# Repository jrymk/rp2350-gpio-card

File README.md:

# rp2350-gpio-card
Expansion Card circuit based on RP2350 for Framework mainboards providing GPIO to the computer. Circuit is based on [Expansion Card template](https://github.com/FrameworkComputer/ExpansionCards) and [RP2350A Minimal board](https://datasheets.raspberrypi.com/rp2350/hardware-design-with-rp2350.pdf). Designed in [KiCad](https://www.kicad.org/). It got produced and assembled. Its fully functional. A 3D case for the card is made by XenoCow and [its files are available on Printables.com](https://www.printables.com/model/1445941-framework-expansion-card-case-for-typec-950-arp24).

## Gallery
* Real photo of card with TYPEC-950-ARP24 produced by NextPCB

* Render of card with Molex 1054440011 (Framework template)

* Render of card with TYPEC-950-ARP24 (NextPCB template)

## GPIO
### Front
| Label | Name   | SPI       | UART       | I2C        | ADC |
| :---- | :----- | :-------- | :--------- | :--------- | :-- |
| 0     | GPIO0  | SPI0 RX   | UART0 TX   | I2C0 SDA   |     |
| 1     | GPIO1  | SPI0 CSn  | UART0 RX   | I2C0 SCL   |     |
| 2     | GPIO2  | SPI0 SCK  |            | I2C1 SDA   |     |
| 3     | GPIO3  | SPI0 TX   |            | I2C1 SCL   |     |
| 4     | GPIO4  | SPI0 RX   | UART1 TX   | I2C0 SDA   |     |
| 5     | GPIO5  | SPI0 CSn  | UART1 RX   | I2C0 SCL   |     |
| 6     | GPIO6  | SPI0 SCK  |            | I2C1 SDA   |     |
| 7     | GPIO7  | SPI0 TX   |            | I2C1 SCL   |     |
| VCC   | 3.3v   |           |            |            |     |
| R     | Reset  |           |            |            |     |

### Back
| Label | Name   | SPI       | UART       | I2C        | ADC   |
| :---- | :----- | :-------- | :--------- | :--------- | :---- |
| 29    | GPIO29 |           |            |            | ADC3  |
| 28    | GPIO28 |           |            |            | ADC2  |
| 27    | GPIO27 |           |            | I2C1 SDL   | ADC1  |
| G     | Ground |           |            |            |       |
| 13    | GPIO13 | SPI1 CSN  | UART0 RX   | I2C0 SCL   |       |
| 12    | GPIO12 | SPI1 RX   | UART0 TX   | I2C0 SDA   |       |
| 11    | GPIO11 | SPI1 TX   |            | I2C1 SCL   |       |
| 10    | GPIO10 | SPI1 SCK  |            | I2C1 SDA   |       |
| 9     | GPIO9  | SPI1 CSn  | UART1 RX   | I2C0 SCL   |       |
| B     | Boot   |           |            |            |       |

## License
Designed by: [Tan Siret Akıncı](https://github.com/tansiret).
Schematics and footprint are licensed with [CC BY 4.0](LICENSE).
Politecnico di Torino name used in this project is © 2025 Politecnico di Torino. The project is sponsored by © 2025 [DeepComputing](https://deepcomputing.io/) and © 2025 [NextPCB](https://www.nextpcb.com/).
The project has been certified by [OSHWA](https://oshwa.org/) as Open Source Hardware (UID: [IT000024](https://certification.oshwa.org/it000024.html)).
</br>

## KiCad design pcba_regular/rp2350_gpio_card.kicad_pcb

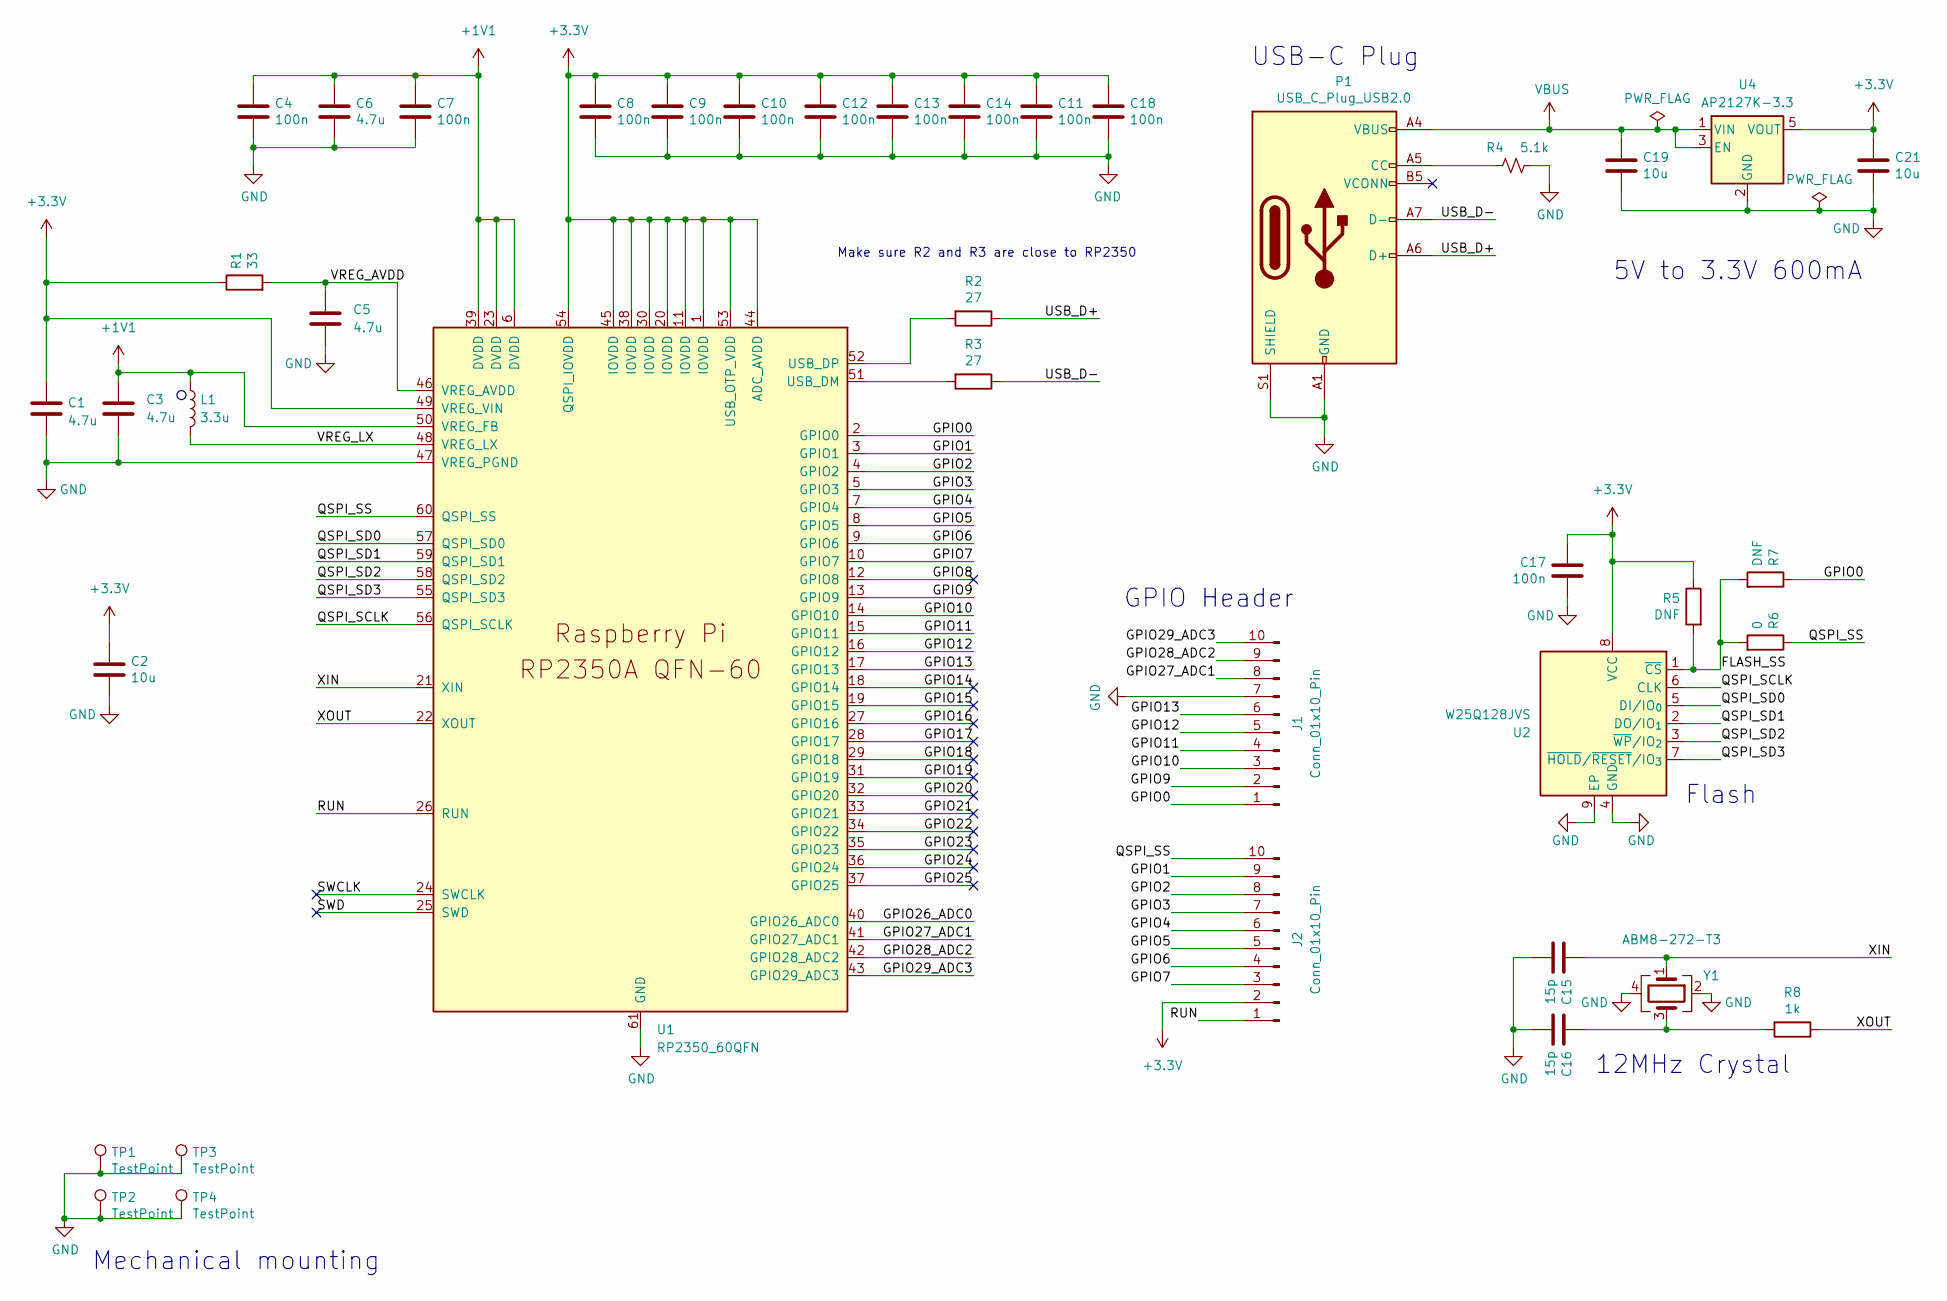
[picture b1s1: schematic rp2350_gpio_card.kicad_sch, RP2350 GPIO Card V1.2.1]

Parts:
C1, C3: 4.7u; C_0402_1005Metric_small_pads
C2, C19, C21: 10u; C_0805_2012Metric
C4, C7, C8, C9, C10, C11, C12, C13, C14, C17, C18: 100n; C_0402_1005Metric
C5, C6: 4.7u; C_0402_1005Metric
C15, C16: 15p; C_0402_1005Metric
J1, J2: Conn_01x10_Pin; Custom_Harwin_M20-89010xx_1x10_P2.54mm_Horizontal
L1: 3.3u; L_pol_2016
P1: USB_C_Plug_USB2.0; USB_C_Plug_Molex_105444
R1: 33; R_0402_1005Metric
R2, R3: 27; R_0402_1005Metric
R4: 5.1k; R_0402_1005Metric
R5, R7: DNF; R_0402_1005Metric
R6: 0; R_0402_1005Metric
R8: 1k; R_0402_1005Metric
TP1, TP2, TP3, TP4: TestPoint; TestPoint_Pad_1.5x1.5mm
U1: RP2350_60QFN; RP2350-QFN-60-1EP_7x7_P0.4mm_EP3.4x3.4mm_ThermalVias
U2: W25Q128JVS; WSON-8-1EP_6x5mm_P1.27mm_EP3.4x4.3mm
U4: AP2127K-3.3; SOT-23-5
Y1: ABM8-272-T3; Crystal_SMD_3225-4Pin_3.2x2.5mm

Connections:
+1V1: C3.1, C4.1, C6.1, C7.1, L1.1, U1.6 (DVDD), U1.23 (DVDD), U1.39 (DVDD), U1.50 (VREG_FB)
+3.3V: C1.1, C2.1, C8.1, C9.1, C10.1, C11.1, C12.1, C13.1, C14.1, C17.1, C18.1, C21.1, J2.2, R1.1, R5.1, U1.1 (IOVDD), U1.11 (IOVDD), U1.20 (IOVDD), U1.30 (IOVDD), U1.38 (IOVDD), U1.44 (ADC_AVDD), U1.45 (IOVDD), U1.49 (VREG_VIN), U1.53 (USB_OTP_VDD), U1.54 (QSPI_IOVDD), U2.8 (VCC), U4.5 (VOUT)
/FLASH_SS: R5.2, R6.2, R7.2, U2.1 (~CS)
/GPIO0: J1.1, R7.1, U1.2 (GPIO0)
/GPIO1: J2.9, U1.3 (GPIO1)
/GPIO2: J2.8, U1.4 (GPIO2)
/GPIO3: J2.7, U1.5 (GPIO3)
/GPIO4: J2.6, U1.7 (GPIO4)
/GPIO5: J2.5, U1.8 (GPIO5)
/GPIO6: J2.4, U1.9 (GPIO6)
/GPIO7: J2.3, U1.10 (GPIO7)
/GPIO8: U1.12 (GPIO8)
/GPIO9: J1.2, U1.13 (GPIO9)
/GPIO10: J1.3, U1.14 (GPIO10)
/GPIO11: J1.4, U1.15 (GPIO11)
/GPIO12: J1.5, U1.16 (GPIO12)
/GPIO13: J1.6, U1.17 (GPIO13)
/GPIO14: U1.18 (GPIO14)
/GPIO15: U1.19 (GPIO15)
/GPIO16: U1.27 (GPIO16)
/GPIO17: U1.28 (GPIO17)
/GPIO18: U1.29 (GPIO18)
/GPIO19: U1.31 (GPIO19)
/GPIO20: U1.32 (GPIO20)
/GPIO21: U1.33 (GPIO21)
/GPIO22: U1.34 (GPIO22)
/GPIO23: U1.35 (GPIO23)
/GPIO24: U1.36 (GPIO24)
/GPIO25: U1.37 (GPIO25)
/GPIO26_ADC0: U1.40 (GPIO26_ADC0)
/GPIO27_ADC1: J1.8, U1.41 (GPIO27_ADC1)
/GPIO28_ADC2: J1.9, U1.42 (GPIO28_ADC2)
/GPIO29_ADC3: J1.10, U1.43 (GPIO29_ADC3)
/QSPI_SCLK: U1.56 (QSPI_SCLK), U2.6 (CLK)
/QSPI_SD0: U1.57 (QSPI_SD0), U2.5 (DI/IO_{0})
/QSPI_SD1: U1.59 (QSPI_SD1), U2.2 (DO/IO_{1})
/QSPI_SD2: U1.58 (QSPI_SD2), U2.3 (~WP/IO_{2})
/QSPI_SD3: U1.55 (QSPI_SD3), U2.7 (~HOLD/~RESET/IO_{3})
/QSPI_SS: J2.10, R6.1, U1.60 (QSPI_SS)
/RUN: J2.1, U1.26 (RUN)
/SWCLK: U1.24 (SWCLK)
/SWD: U1.25 (SWD)
/USB_D+: P1.A6 (D+), R2.1
/USB_D-: P1.A7 (D-), R3.1
/VREG_AVDD: C5.1, R1.2, U1.46 (VREG_AVDD)
/VREG_LX: L1.2, U1.48 (VREG_LX)
/XIN: C15.1, U1.21 (XIN), Y1.1
/XOUT: R8.1, U1.22 (XOUT)
GND: C1.2, C2.2, C3.2, C4.2, C5.2, C6.2, C7.2, C8.2, C9.2, C10.2, C11.2, C12.2, C13.2, C14.2, C15.2, C16.2, C17.2, C18.2, C19.2, C21.2, J1.7, P1.A1 (GND), P1.A12 (GND), P1.B1 (GND), P1.B12 (GND), P1.S1 (SHIELD), R4.2, TP1.1, TP2.1, TP3.1, TP4.1, U1.47 (VREG_PGND), U1.61 (GND), U2.4 (GND), U2.9 (EP), U4.2 (GND), Y1.2, Y1.4
unnamed: C16.1, R8.2, Y1.3
unnamed: P1.A5 (CC), R4.1
unnamed: R3.2, U1.51 (USB_DM)
unnamed: R2.2, U1.52 (USB_DP)
VBUS: C19.1, P1.A4 (VBUS), P1.A9 (VBUS), P1.B4 (VBUS), P1.B9 (VBUS), U4.1 (VIN), U4.3 (EN)

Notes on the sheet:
GPIO Header
5V to 3.3V 600mA
USB-C Plug
Mechanical mounting
12MHz Crystal
Flash
Make sure R2 and R3 are close to RP2350

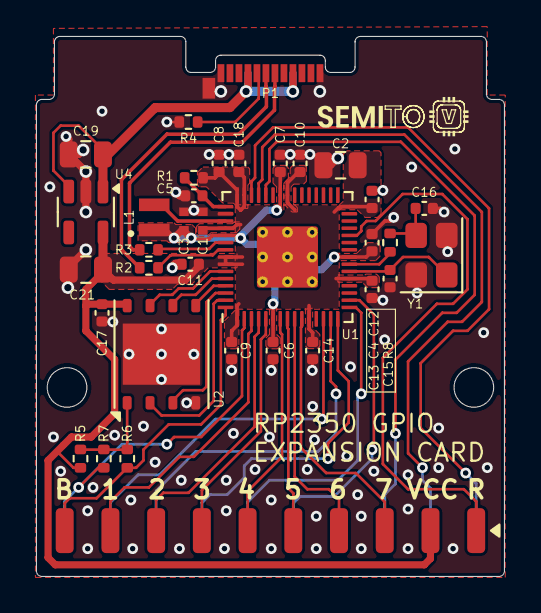
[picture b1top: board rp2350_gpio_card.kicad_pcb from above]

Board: 2 copper layers, 26.0 x 30.0 mm, 38 parts (1 on the bottom side), 38 nets.

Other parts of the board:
H1, H2: MountingHole; MountingHole_2.2mm_M2

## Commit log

2025-10-07 add real photo
2025-12-10 optimized PCB layout
2025-12-10 optimized back gnd plane
2025-12-10 added open hardware graphics back
2025-12-10 clean up
2025-12-11 fix DRC errors and increase clearances

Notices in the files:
pcba_regular/rp2350_gpio_card.kicad_pcb:
This work is licensed under a Creative Commons Attribution 4.0 International License
License: CC BY 4.0
